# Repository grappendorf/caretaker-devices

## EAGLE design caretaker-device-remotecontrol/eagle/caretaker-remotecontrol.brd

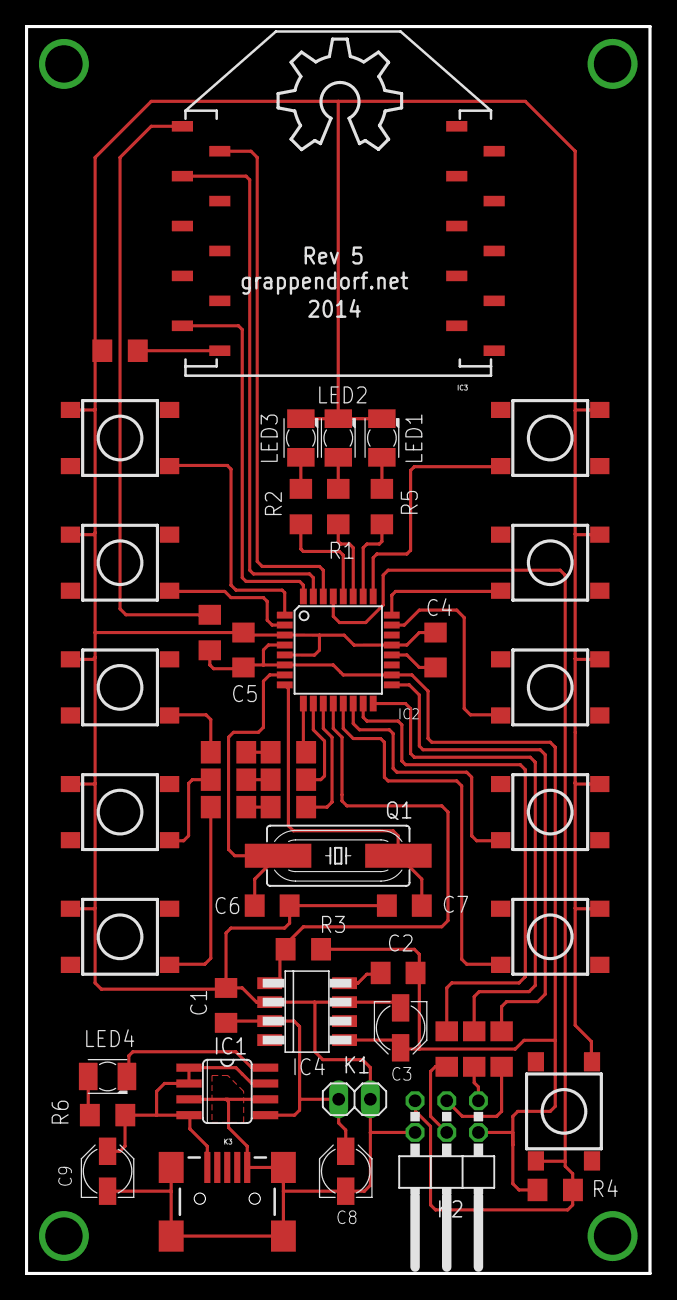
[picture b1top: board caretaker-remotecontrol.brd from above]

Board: 2 copper layers, 50.0 x 100.0 mm, 50 parts (0 on the bottom side), 45 nets.

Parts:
C1, C4, C5: 100n; C1206
C2: 10p; C1206
C3: 1u/16V; PANASONIC_B
C6, C7: 22p; C1206
C8, C9: 10u/16V; PANASONIC_B
IC1: MAX1811N; SO08
IC2: ATMEGA168; TQFP32-08
IC3: XBee Series 2; XBEE-SMD
IC4: ZLDO330; SM8
K1: BAT; 1X02
K2: ISP; 2X03/90
K3: USB-MINIB-5PIN; USB-MINIB
LED1, LED2, LED3, LED4: KA-3528ASYC
LOGO1: OSHW_LOGO_10MILX0350-NT; OSHW_10X350_NOTEXT
Q1: 16MHz; HC49UP
R1, R2, R5: 180; R1206
R3: 100k; R1206
R4: 10k; R1206
R6: 1k; R1206
R7, R8, R9, R10, R11, R12, R13, R14, R15, R16, R17: 0; R1206
RESET: TACTILE_SWITCH_TALL
S1, S2, S3, S4, S5, S6, S7, S8, S9, S10: TACTILE_SWITCH_TALL

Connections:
+3V3: C2.2, C3.+, C5.1, IC2.4, IC2.6, IC2.18, IC4.5, K2.2, R3.1, R4.1, R14.2
BAT: C1.1, C8.+, IC1.5, IC4.3, K1.1
GND: C1.2, C3.-, C4.2, C5.2, C6.1, C7.1, C8.-, C9.-, IC1.3, IC1.6, IC2.3, IC2.5, IC2.21, IC4.2, IC4.7, K1.2, K2.6, K3.GND, K3.MTN1, K3.MTN2, K3.MTN3, K3.MTN4, LED1.C, LED2.C, LED3.C, R13.1, RESET.A2, S1.B1, S2.B1, S3.B1, S4.B1, S5.B1, S6.B2, S7.B2, S8.B2, S9.B2, S10.B2
LED1: IC2.26, R5.1
LED2: IC2.27, R1.1
LED3: IC2.28, R2.1
LOWBAT: IC2.12, IC4.1, R3.2
MISO: IC2.16, R15.2
MOSI: IC2.15, R17.1
unnamed: C9.+, IC1.1, IC1.2, IC1.4, IC1.7, K3.VBUS, R6.2
unnamed: C4.1, IC2.20
unnamed: C6.2, IC2.7, Q1.2
unnamed: C7.2, IC2.8, Q1.1
unnamed: LED2.A, R1.2
unnamed: LED3.A, R2.2
unnamed: LED4.A, R6.1
unnamed: LED1.A, R5.2
unnamed: IC1.8, LED4.C
unnamed: C2.1, IC4.8
unnamed: R8.2, S3.A2
unnamed: R10.2, S4.A2
unnamed: R12.2, S5.A2
unnamed: R7.2, R8.1
unnamed: R9.2, R10.1
unnamed: R11.2, R12.1
unnamed: IC3.10, R13.2
unnamed: IC3.1, R14.1
unnamed: K2.1, R15.1
unnamed: K2.3, R16.1
unnamed: K2.4, R17.2
RESET: IC2.29, K2.5, R4.2, RESET.B1
RXD: IC2.30, IC3.2
SCK: IC2.17, R16.2
SW1: IC2.1, S1.A2
SW2: IC2.2, S2.A2
SW3: IC2.9, R7.1
SW4: IC2.10, R9.1
SW5: IC2.11, R11.1
SW6: IC2.25, S6.A1
SW7: IC2.24, S7.A1
SW8: IC2.23, S8.A1
SW9: IC2.14, S9.A1
SW10: IC2.13, S10.A1
TXD: IC2.31, IC3.3
XBEESLEEP: IC2.32, IC3.9
